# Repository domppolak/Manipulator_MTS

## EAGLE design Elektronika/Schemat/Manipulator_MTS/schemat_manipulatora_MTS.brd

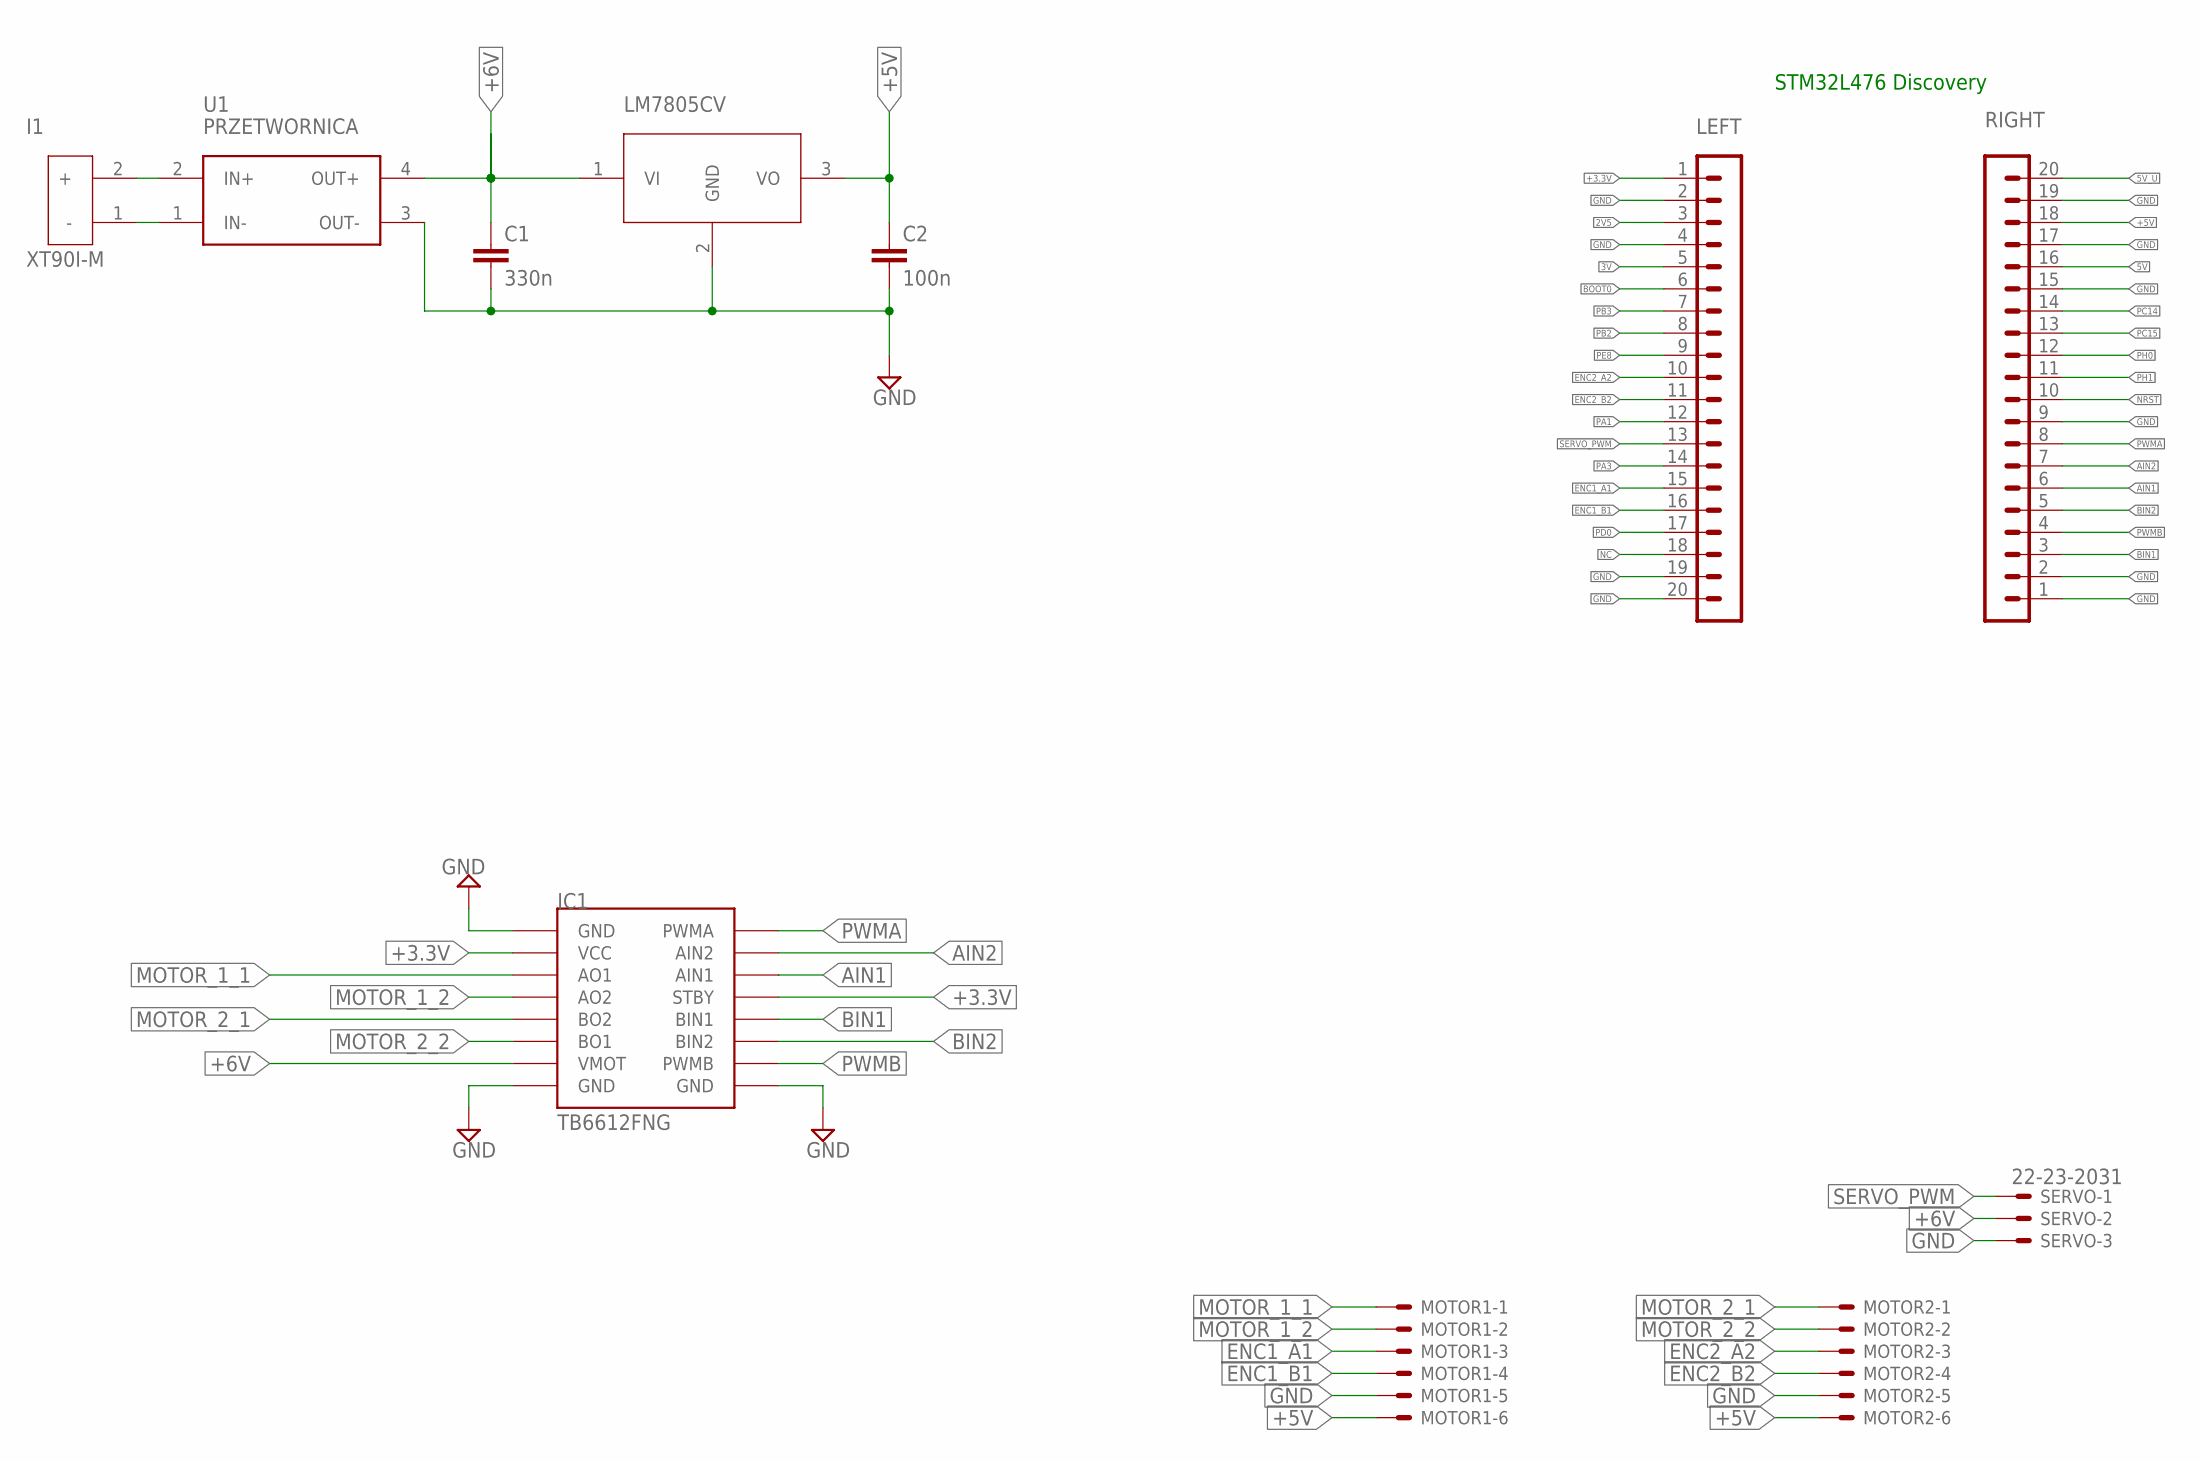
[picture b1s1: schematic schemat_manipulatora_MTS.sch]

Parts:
C1: 330n; C025-024X044
C2: 100n; C025-024X044
I1: XT90I-M
IC1: MODUL_POLOLU
LEFT: MA20-1
LM7805CV: LM7805CV; TO220V
MOTOR1, MOTOR2: 22-23-2061
RIGHT: MA20-1
SERVO: 22-23-2031
U1: PRZETWORNICA; BUCK_MODULE

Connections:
2V5: LEFT.3
3V: LEFT.5
5V: RIGHT.16
5V_U: RIGHT.20
+3.3V: IC1.STBY, IC1.VCC, LEFT.1
+5V: C2.1, LM7805CV.3 (VO), MOTOR1.6, MOTOR2.6, RIGHT.18
+6V: C1.1, IC1.VMOT, LM7805CV.1 (VI), SERVO.2, U1.4 (OUT+)
AIN1: IC1.AIN1, RIGHT.6
AIN2: IC1.AIN2, RIGHT.7
BIN1: IC1.BIN1, RIGHT.3
BIN2: IC1.BIN2, RIGHT.5
BOOT0: LEFT.6
ENC1_A1: LEFT.15, MOTOR1.3
ENC1_B1: LEFT.16, MOTOR1.4
ENC2_A2: LEFT.10, MOTOR2.3
ENC2_B2: LEFT.11, MOTOR2.4
GND: C1.2, C2.2, IC1.GND1 (GND), IC1.GND2 (GND), IC1.GND3 (GND), LEFT.2, LEFT.4, LEFT.19, LEFT.20, LM7805CV.2 (GND), MOTOR1.5, MOTOR2.5, RIGHT.1, RIGHT.2, RIGHT.9, RIGHT.15, RIGHT.17, RIGHT.19, SERVO.3, U1.3 (OUT-)
MOTOR_1_1: IC1.AO1, MOTOR1.1
MOTOR_1_2: IC1.A02 (AO2), MOTOR1.2
MOTOR_2_1: IC1.BO2, MOTOR2.1
MOTOR_2_2: IC1.BO1, MOTOR2.2
unnamed: I1.2 (+), U1.2 (IN+)
unnamed: I1.1 (-), U1.1 (IN-)
NC: LEFT.18
NRST: RIGHT.10
PA1: LEFT.12
PA3: LEFT.14
PB2: LEFT.8
PB3: LEFT.7
PC14: RIGHT.14
PC15: RIGHT.13
PD0: LEFT.17
PE8: LEFT.9
PH0: RIGHT.12
PH1: RIGHT.11
PWMA: IC1.PWMA, RIGHT.8
PWMB: IC1.PWMB, RIGHT.4
SERVO_PWM: LEFT.13, SERVO.1

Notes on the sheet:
STM32L476 Discovery

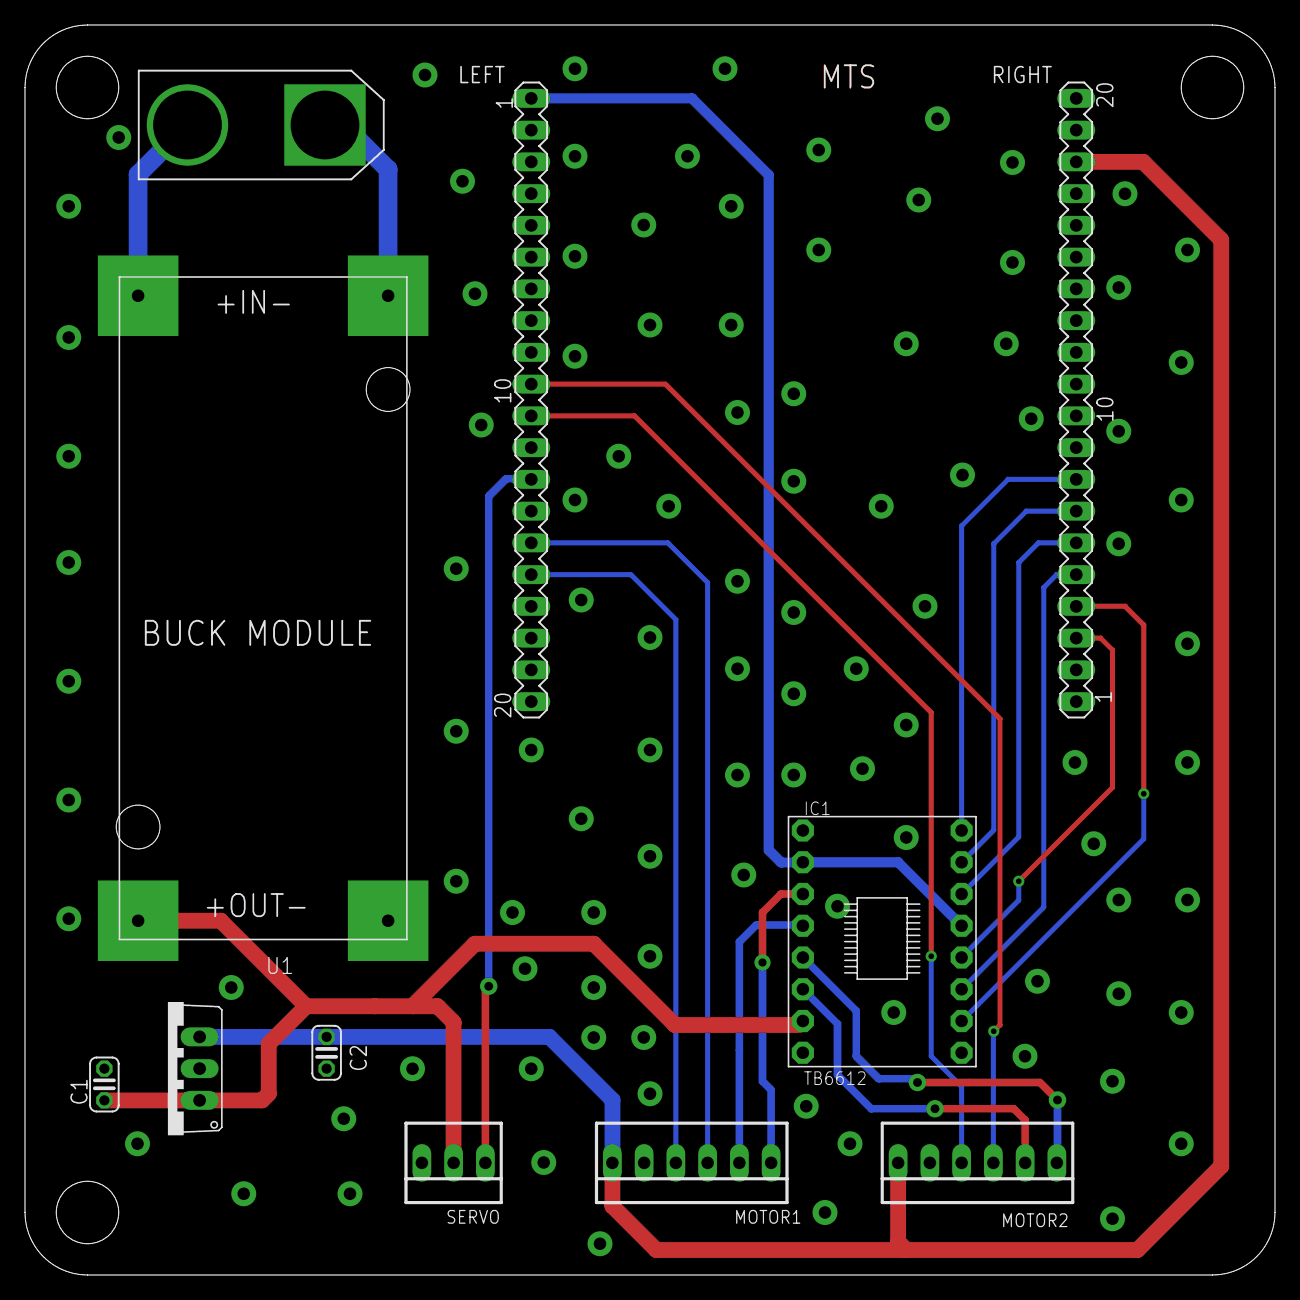
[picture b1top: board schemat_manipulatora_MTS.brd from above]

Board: 2 copper layers, 100.0 x 100.0 mm, 11 parts (0 on the bottom side), 21 nets.

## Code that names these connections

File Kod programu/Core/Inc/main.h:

/* USER CODE BEGIN Header */
/**
  ******************************************************************************
  * @file           : main.h
  * @brief          : Header for main.c file.
  *                   This file contains the common defines of the application.
  ******************************************************************************
  * @attention
  *
  * Copyright (c) 2022 STMicroelectronics.
  * All rights reserved.
  *
  * This software is licensed under terms that can be found in the LICENSE file
  * in the root directory of this software component.
  * If no LICENSE file comes with this software, it is provided AS-IS.
  *
  ******************************************************************************
  */
/* USER CODE END Header */

/* Define to prevent recursive inclusion -------------------------------------*/
#ifndef __MAIN_H
#define __MAIN_H

#ifdef __cplusplus
extern "C" {
#endif

/* Includes ------------------------------------------------------------------*/
#include "stm32l4xx_hal.h"

/* Private includes ----------------------------------------------------------*/
/* USER CODE BEGIN Includes */

/* USER CODE END Includes */

/* Exported types ------------------------------------------------------------*/
/* USER CODE BEGIN ET */

/* USER CODE END ET */

/* Exported constants --------------------------------------------------------*/
/* USER CODE BEGIN EC */

/* USER CODE END EC */

/* Exported macro ------------------------------------------------------------*/
/* USER CODE BEGIN EM */

/* USER CODE END EM */

/* Exported functions prototypes ---------------------------------------------*/
void Error_Handler(void);

/* USER CODE BEGIN EFP */

/* USER CODE END EFP */

/* Private defines -----------------------------------------------------------*/
#define ENC2_A2_Pin GPIO_PIN_0
#define ENC2_A2_GPIO_Port GPIOA
#define ENC2_B2_Pin GPIO_PIN_1
#define ENC2_B2_GPIO_Port GPIOA
#define SERVO_PWM_Pin GPIO_PIN_2
#define SERVO_PWM_GPIO_Port GPIOA
#define AIN2_Pin GPIO_PIN_10
#define AIN2_GPIO_Port GPIOE
#define PWMA_Pin GPIO_PIN_11
#define PWMA_GPIO_Port GPIOE
#define AIN1_Pin GPIO_PIN_12
#define AIN1_GPIO_Port GPIOE
#define BIN2_Pin GPIO_PIN_13
#define BIN2_GPIO_Port GPIOE
#define PWMB_Pin GPIO_PIN_14
#define PWMB_GPIO_Port GPIOE
#define BIN1_Pin GPIO_PIN_15
#define BIN1_GPIO_Port GPIOE
#define ENC1_B1_Pin GPIO_PIN_6
#define ENC1_B1_GPIO_Port GPIOB
#define ENC1_A1_Pin GPIO_PIN_7
#define ENC1_A1_GPIO_Port GPIOB
/* USER CODE BEGIN Private defines */

/* USER CODE END Private defines */

#ifdef __cplusplus
}
#endif

#endif /* __MAIN_H */

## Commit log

2022-04-20 Create Elektronika
2022-04-22 v0.1.0
    dodano:
    - schemat połączeń elektronicznych
2022-04-22 v0.1.0
    Dodano:
    - dokumentację części
2022-04-22 v0.1.0
    Dodano:
    - konfigurację mikrokontrolera
2022-04-24 ver 0.1.0
    Dodano:
    - Kinematykę manipulatora
2022-04-24 v0.1.1
    Dodano:
    - konfigurację Timerów
2022-04-25 v0.1.1
    Dodano:
    - dokumentację płytki STM32L476VG Discovery
    - projekt płytki PCB
    - poprawiono kofigurację mikrokotrolera
2022-04-28 v0.1.1
    Dodano:
    - w pełni stworzony model płytki PCB
2022-05-04 Konstrukcja manipulatora
2022-05-04 Add files via upload
    Zdjęcia podłączonej elektroniki (bez generatora)
2022-05-04 Schemat elektroniki w formacie PDF
2022-05-04 Schemat elektroniki w PNG
2022-05-27 Poprawiona konfiguracja timerów
2022-05-29 implementacja regulatora pid
2022-05-29 sterowanie silnikami, PID
2022-05-29 Algorytm FABRIK
2022-05-29 Poprawka błędu przy mergowaniu
2022-06-05 Testowanie algorytmu FABRIK
2022-06-06 Zmiana algorytmu wyliczania kinematyki odwrotnej na zależności geometryczne
2022-06-10 poprawa sterownia silnikami
2022-06-10 Poprawa geometrika
2022-06-11 Dodanie nastaw PID oraz poprawna kompilacja projektu
2022-06-12 Szybkie poprawki
2022-06-12 sterowanie silnikami ver 2
2022-06-12 poprawa błędów kompilacji
2022-06-12 interfejs sterowania ver 1
2022-06-13 próba komunikacji
2022-06-13 komunikacja, sterowanie 2 silnikami
